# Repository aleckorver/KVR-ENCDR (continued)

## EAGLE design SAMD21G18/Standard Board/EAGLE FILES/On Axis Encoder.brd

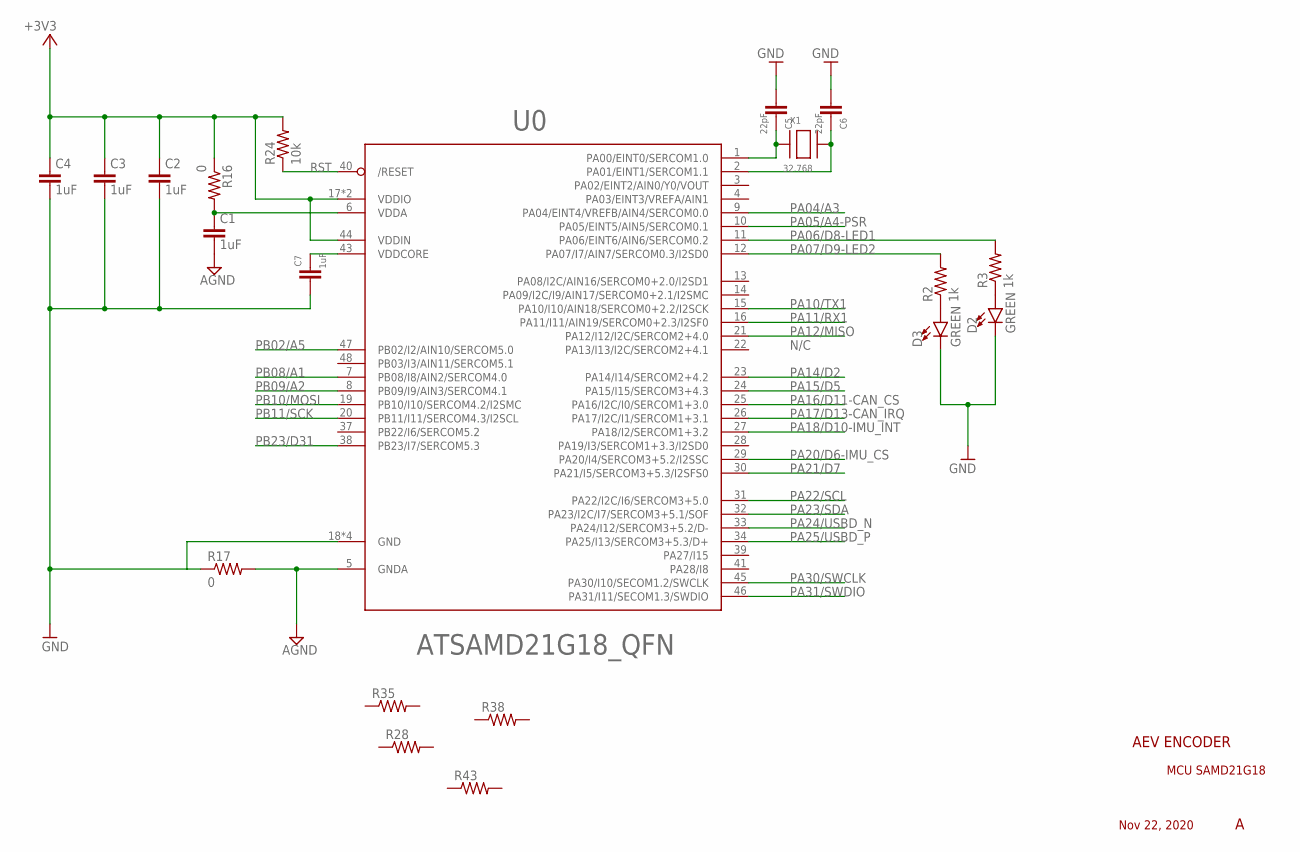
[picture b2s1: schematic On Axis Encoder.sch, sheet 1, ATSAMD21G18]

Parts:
C1, C2, C3, C4, C7: 1uF; C0805
C5, C6: 22pF; C0805
D2, D3: GREEN; LED-0603
R2, R3: 1k; R0603
R16, R17: 0; R0805
R24: 10k; R0805
R28: R-US_R0603; R0603
R35: R-US_R0402; R0402
R38: R-US_R0201; R0201
R43: R-US_R0805; R0805
U0: ATSAMD21G18_QFN; MICROBUILDER_TQFN48_7MM
X1: 32.768; XTAL3215

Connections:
+3V3: C2.1, C3.1, C4.1, R16.1, R24.2, U0.17 (VDDIO), U0.36 (VDDIO), U0.44 (VDDIN); also elsewhere on the board
AGND: C1.2, R17.2, U0.5 (GNDA); also elsewhere on the board
GND: C2.2, C3.2, C4.2, C5.2, C6.2, C7.2, D2.C, D3.C, R17.1, U0.18 (GND), U0.35 (GND), U0.42 (GND), U0.THERMAL (GND); also elsewhere on the board
unnamed: D2.A, R3.1
unnamed: D3.A, R2.1
unnamed: C5.1, U0.1 (PA00/EINT0/SERCOM1.0), X1.P$1
unnamed: C6.1, U0.2 (PA01/EINT1/SERCOM1.1), X1.P$2
unnamed: C1.1, R16.2, U0.6 (VDDA)
PA04/A3: U0.9 (PA04/EINT4/VREFB/AIN4/SERCOM0.0)
PA05/A4-PSR: U0.10 (PA05/EINT5/AIN5/SERCOM0.1); also elsewhere on the board
PA06/D8-LED1: R3.2, U0.11 (PA06/EINT6/AIN6/SERCOM0.2)
PA07/D9-LED2: R2.2, U0.12 (PA07/I7/AIN7/SERCOM0.3/I2SD0)
PA10/TX1: U0.15 (PA10/I10/AIN18/SERCOM0+2.2/I2SCK)
PA11/RX1: U0.16 (PA11/I11/AIN19/SERCOM0+2.3/I2SF0)
PA12/MISO: U0.21 (PA12/I12/I2C/SERCOM2+4.0); also elsewhere on the board
PA14/D2: U0.23 (PA14/I14/SERCOM2+4.2)
PA15/D5: U0.24 (PA15/I15/SERCOM3+4.3)
PA16/D11-CAN_CS: U0.25 (PA16/I2C/I0/SERCOM1+3.0); also elsewhere on the board
PA17/D13-CAN_IRQ: U0.26 (PA17/I2C/I1/SERCOM1+3.1); also elsewhere on the board
PA18/D10-IMU_INT: U0.27 (PA18/I2/SERCOM1+3.2); also elsewhere on the board
PA20/D6-IMU_CS: U0.29 (PA20/I4/SERCOM3+5.2/I2SSC); also elsewhere on the board
PA21/D7: U0.30 (PA21/I5/SERCOM3+5.3/I2SFS0)
PA22/SCL: U0.31 (PA22/I2C/I6/SERCOM3+5.0); also elsewhere on the board
PA23/SDA: U0.32 (PA23/I2C/I7/SERCOM3+5.1/SOF); also elsewhere on the board
PA24/USBD_N: U0.33 (PA24/I12/SERCOM3+5.2/D-); also elsewhere on the board
PA25/USBD_P: U0.34 (PA25/I13/SERCOM3+5.3/D+); also elsewhere on the board
PA30/SWCLK: U0.45 (PA30/I10/SECOM1.2/SWCLK); also elsewhere on the board
PA31/SWDIO: U0.46 (PA31/I11/SECOM1.3/SWDIO); also elsewhere on the board
PB02/A5: U0.47 (PB02/I2/AIN10/SERCOM5.0)
PB08/A1: U0.7 (PB08/I8/AIN2/SERCOM4.0)
PB09/A2: U0.8 (PB09/I9/AIN3/SERCOM4.1)
PB10/MOSI: U0.19 (PB10/I10/SERCOM4.2/I2SMC); also elsewhere on the board
PB11/SCK: U0.20 (PB11/I11/SERCOM4.3/I2SCL); also elsewhere on the board
PB23/D31: U0.38 (PB23/I7/SERCOM5.3)
RST: R24.1, U0.40 (/RESET); also elsewhere on the board
VDDCORE2: C7.1, U0.43 (VDDCORE)

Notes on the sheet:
N/C
AEV ENCODER
MCU SAMD21G18
Nov 22, 2020

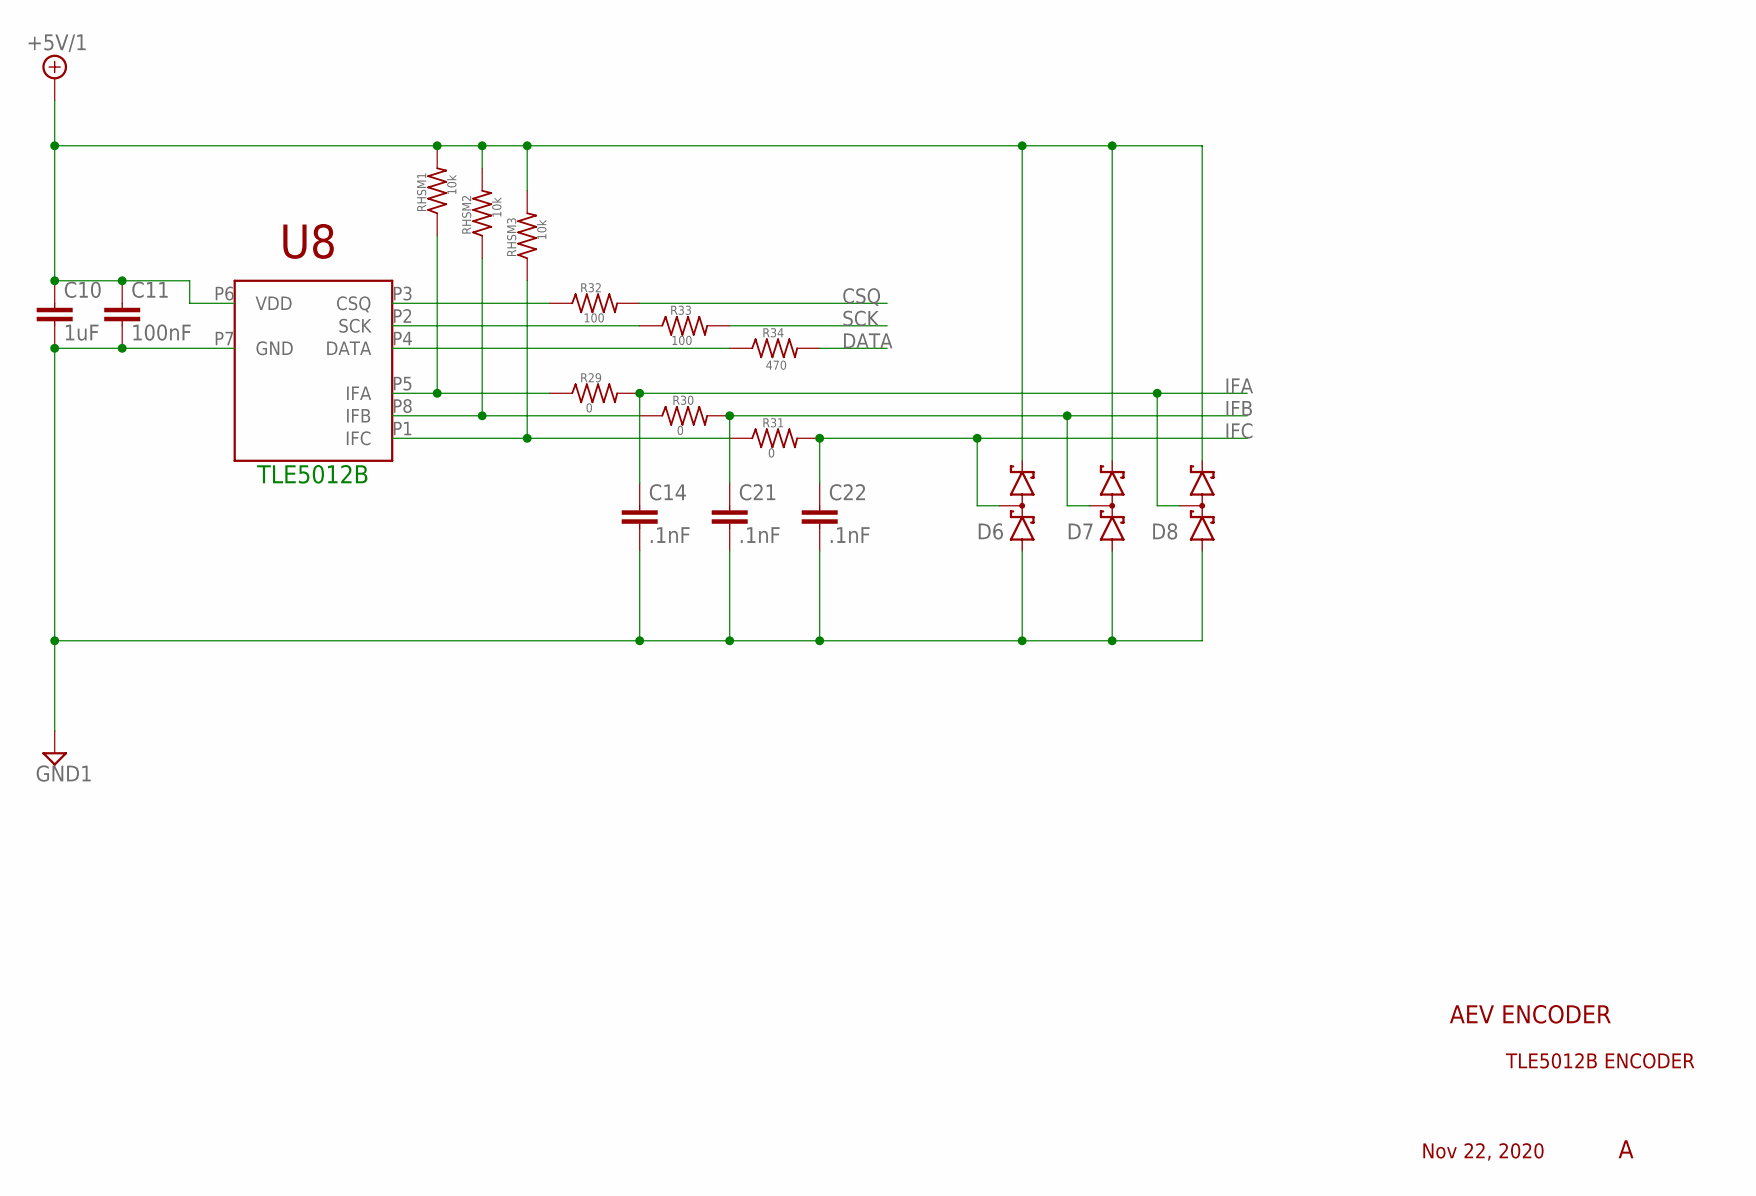
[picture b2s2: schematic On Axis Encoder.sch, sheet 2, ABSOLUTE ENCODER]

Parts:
C10: 1uF; C0805
C11: 100nF; C0805
C14, C21, C22: .1nF; C0805
D6, D7, D8: BAS70-04; SOT23
R29, R30, R31: 0; R0805
R32, R33: 100; R0805
R34: 470; R0805
RHSM1, RHSM2, RHSM3: 10k; R0805
U8: TLE5012B; PG-DSO-8

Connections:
+5V/1: C10.1, C11.1, D6.2 (C2), D7.2 (C2), D8.2 (C2), RHSM1.2, RHSM2.2, RHSM3.2, U8.P6 (VDD); also elsewhere on the board
CSQ: R32.2; also elsewhere on the board
DATA: R34.2; also elsewhere on the board
GND1: C10.2, C11.2, C14.2, C21.2, C22.2, D6.1 (A1), D7.1 (A1), D8.1 (A1), U8.P7 (GND); also elsewhere on the board
IFA: C14.1, D8.3 (C1A2), R29.2; also elsewhere on the board
IFB: C21.1, D7.3 (C1A2), R30.2; also elsewhere on the board
IFC: C22.1, D6.3 (C1A2), R31.2; also elsewhere on the board
unnamed: R32.1, U8.P3 (CSQ)
unnamed: R33.1, U8.P2 (SCK)
unnamed: R34.1, U8.P4 (DATA)
unnamed: R29.1, RHSM1.1, U8.P5 (IFA)
unnamed: R30.1, RHSM2.1, U8.P8 (IFB)
unnamed: R31.1, RHSM3.1, U8.P1 (IFC)
SCK: R33.2; also elsewhere on the board

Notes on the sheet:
TLE5012B
AEV ENCODER
TLE5012B ENCODER
Nov 22, 2020

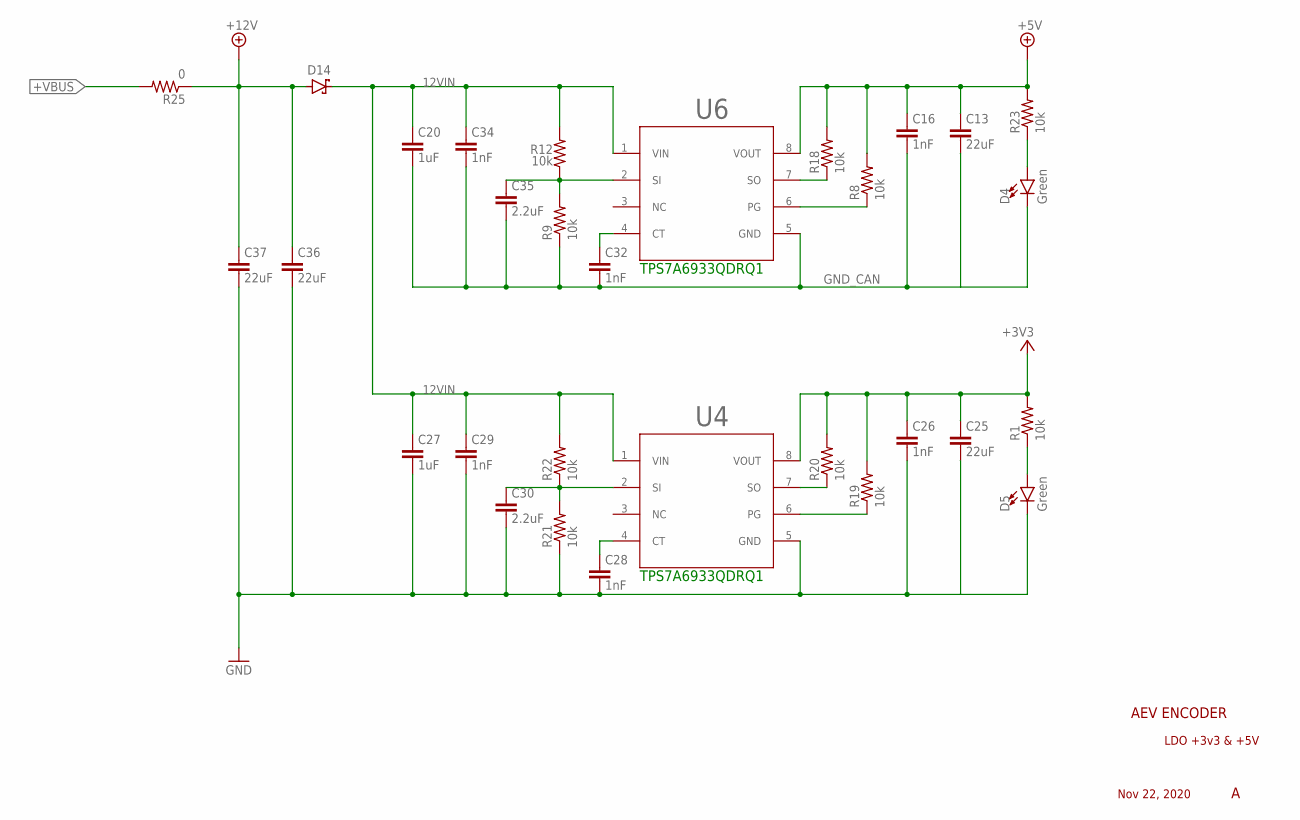
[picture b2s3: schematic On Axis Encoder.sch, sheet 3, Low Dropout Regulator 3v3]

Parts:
C13, C25: 22uF; C0805
C16, C26, C28, C29, C32, C34: 1nF; C0805
C20, C27: 1uF; C0805
C30, C35: 2.2uF; C0805
C36, C37: 22uF; C1206
D4, D5: Green; LED-1206-BOTTOM
D14: MBR0520LT1G; SODFL3718X115
R1, R8, R9, R12, R18, R19, R20, R21, R22, R23: 10k; R0805
R25: 0; R0805
U4, U6: Value; D0008A_N

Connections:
12VIN: C20.1, C27.1, C29.1, C34.1, D14.1 (C), R12.2, R22.2, U4.1 (VIN), U6.1 (VIN)
+3V3: C25.1, C26.1, R1.2, R19.2, R20.2, U4.8 (VOUT); also elsewhere on the board
+5V: C13.1, C16.1, R8.2, R18.2, R23.2, U6.8 (VOUT); also elsewhere on the board
+12V: C36.1, C37.1, D14.2 (A), R25.1; also elsewhere on the board
+VBUS: R25.2; also elsewhere on the board
GND: C25.2, C26.2, C27.2, C28.2, C29.2, C30.2, C36.2, C37.2, D5.C, R21.1, U4.5 (GND); also elsewhere on the board
GND_CAN: C13.2, C16.2, C20.2, C32.2, C34.2, C35.2, D4.C, R9.1, U6.5 (GND); also elsewhere on the board
unnamed: D5.A, R1.1
unnamed: C35.1, R9.2, R12.1, U6.2 (SI)
unnamed: C30.1, R21.2, R22.1, U4.2 (SI)
unnamed: R19.1, U4.6 (PG)
unnamed: R20.1, U4.7 (SO)
unnamed: C28.1, U4.4 (CT)
unnamed: R8.1, U6.6 (PG)
unnamed: R18.1, U6.7 (SO)
unnamed: C32.1, U6.4 (CT)
unnamed: D4.A, R23.1

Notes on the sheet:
TPS7A6933QDRQ1
AEV ENCODER
LDO +3v3 & +5V
Nov 22, 2020

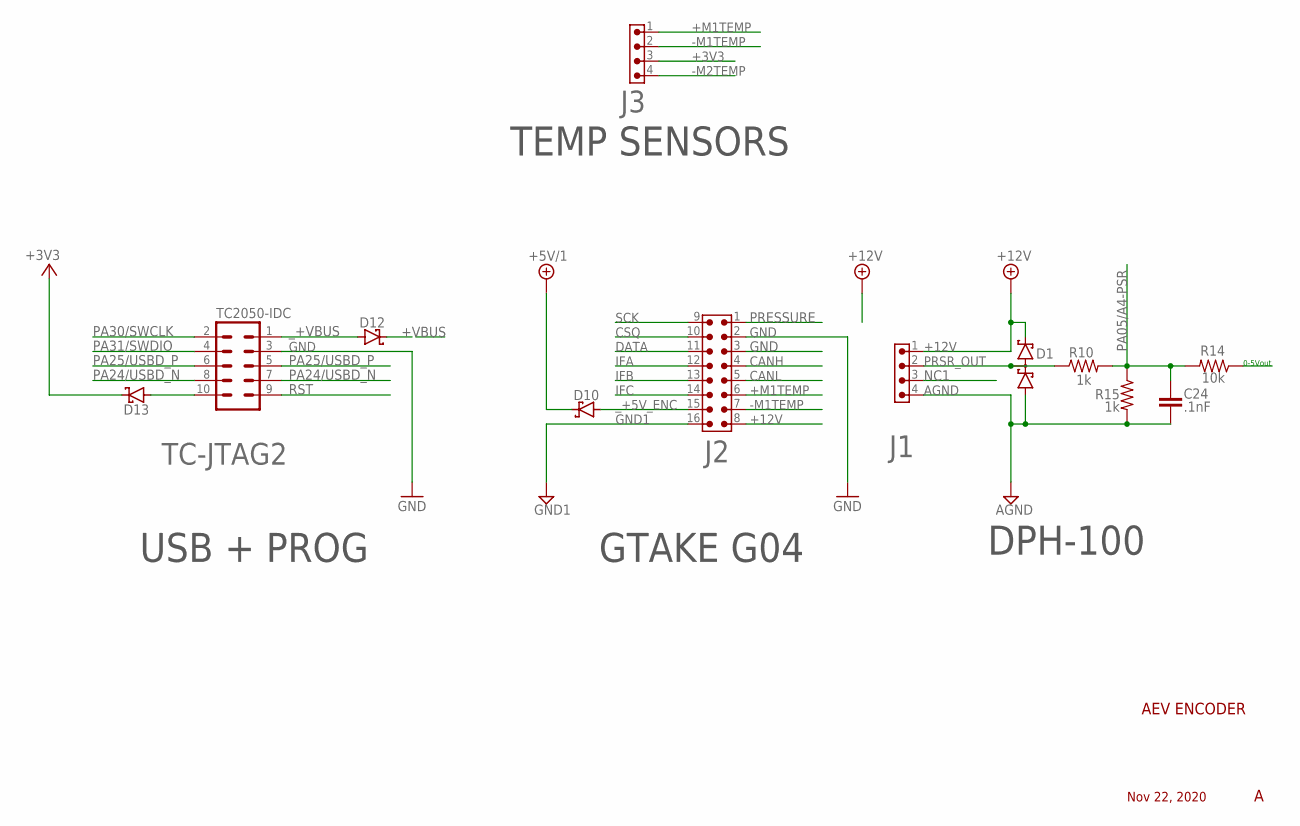
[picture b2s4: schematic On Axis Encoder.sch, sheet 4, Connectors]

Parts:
C24: .1nF; C0805
D1: BAS70-04; SOT23
D10, D12, D13: MBR0520LT1G; SODFL3718X115
J1, J3: 6620XX11122_66200411122; 66200411122
J2: 6620XX21122_66201621122; 66201621122
R10, R15: 1k; R0805
R14: 10k; R0805
TC-JTAG2: TC2050-IDC

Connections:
+3V3: D13.1 (C), J3.3; also elsewhere on the board
+5V/1: D10.1 (C); also elsewhere on the board
+12V: D1.2 (C2), J1.1, J2.8; also elsewhere on the board
+M1TEMP: J2.6, J3.1
+VBUS: D12.1 (C); also elsewhere on the board
-M1TEMP: J2.7, J3.2
-M2TEMP: J3.4; also elsewhere on the board
AGND: C24.2, D1.1 (A1), J1.4, R15.2; also elsewhere on the board
CANH: J2.4; also elsewhere on the board
CANL: J2.5; also elsewhere on the board
CSQ: J2.10; also elsewhere on the board
DATA: J2.11; also elsewhere on the board
GND: J2.2, J2.3, TC-JTAG2.3; also elsewhere on the board
GND1: J2.16; also elsewhere on the board
IFA: J2.12; also elsewhere on the board
IFB: J2.13; also elsewhere on the board
IFC: J2.14; also elsewhere on the board
unnamed: D13.2 (A), TC-JTAG2.10
NC1: J1.3
PA05/A4-PSR: C24.1, R10.2, R14.2, R15.1; also elsewhere on the board
PA24/USBD_N: TC-JTAG2.7, TC-JTAG2.8; also elsewhere on the board
PA25/USBD_P: TC-JTAG2.5, TC-JTAG2.6; also elsewhere on the board
PA30/SWCLK: TC-JTAG2.2; also elsewhere on the board
PA31/SWDIO: TC-JTAG2.4; also elsewhere on the board
PRESSURE: J2.1, R14.1
PRSR_OUT: D1.3 (C1A2), J1.2, R10.1
RST: TC-JTAG2.9; also elsewhere on the board
SCK: J2.9; also elsewhere on the board
_+5V_ENC: D10.2 (A), J2.15
_+VBUS: D12.2 (A), TC-JTAG2.1

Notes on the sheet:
USB + PROG
0-5Vout
AEV ENCODER
Nov 22, 2020
GTAKE G04
DPH-100
TEMP SENSORS

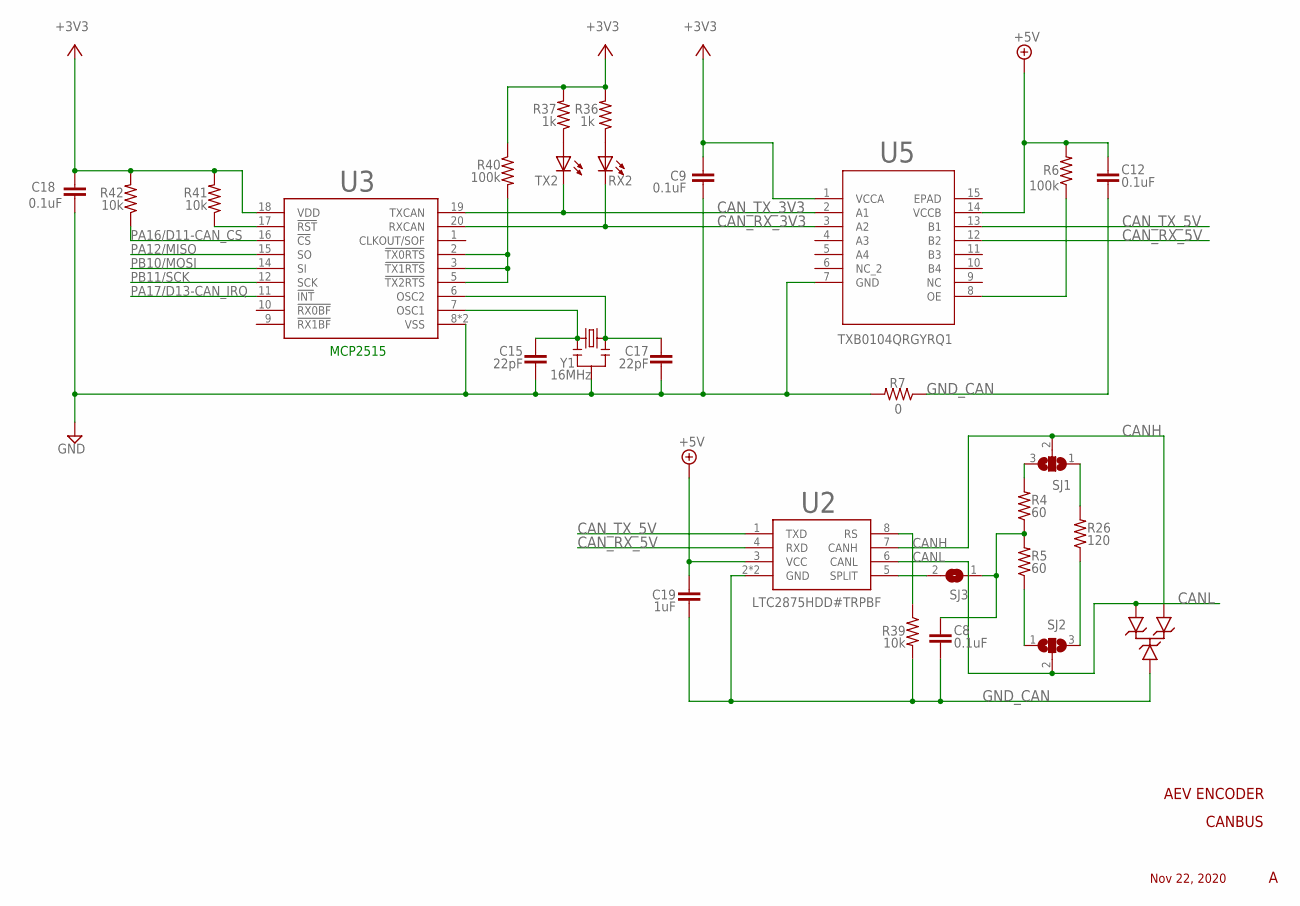
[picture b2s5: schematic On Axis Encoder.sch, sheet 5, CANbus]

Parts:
C8, C9, C12, C18: 0.1uF; C0805
C15, C17: 22pF; C0805
C19: 1uF; C0805
R4, R5: 60; R0805
R6, R40: 100k; R0805
R7: 0; R0805
R26: 120; R0805
R36, R37: 1k; R0805
R39, R41, R42: 10k; R0805
RX2: LEDCHIPLED_0805; CHIPLED_0805
SJ1, SJ2: SJ2W; SJ_2
SJ3: SJ
TX2: LEDCHIPLED_0805; CHIPLED_0805
U2: LTC2875HDD#TRPBF; SON50P300X300X80-9T165X238N
U3: MCP2515-E/ML; QFN50P400X400X100-21T270N
U5: TXB0104QRGYRQ1; RGY14_2P05X2P05
U$2: μCLAMP2492SQ; SOT-23_3L_ONS
Y1: 16MHz; RESONATOR-SMD

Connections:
+3V3: C9.1, C18.1, R36.2, R37.2, R40.1, R41.2, R42.2, U3.18 (VDD), U5.1 (VCCA); also elsewhere on the board
+5V: C12.1, C19.1, R6.2, U2.3 (VCC), U5.14 (VCCB); also elsewhere on the board
CANH: SJ1.2, U2.7 (CANH), U$2.2; also elsewhere on the board
CANL: SJ2.2, U2.6 (CANL), U$2.1; also elsewhere on the board
CAN_RX_3V3: RX2.C, U3.20 (RXCAN), U5.3 (A2)
CAN_RX_5V: U2.4 (RXD), U5.12 (B2)
CAN_TX_3V3: TX2.C, U3.19 (TXCAN), U5.2 (A1)
CAN_TX_5V: U2.1 (TXD), U5.13 (B1)
GND: C9.2, C15.2, C17.2, C18.2, R7.2, U3.8 (VSS), U3.21 (VSS), U5.7 (GND), Y1.2; also elsewhere on the board
GND_CAN: C8.2, C12.2, C19.2, R7.1, R39.2, U2.2 (GND), U2.9 (GND), U$2.3; also elsewhere on the board
unnamed: R6.1, U5.8 (OE)
unnamed: R39.1, U2.8 (RS)
unnamed: SJ3.2, U2.5 (SPLIT)
unnamed: R36.1, RX2.A
unnamed: R37.1, TX2.A
unnamed: R41.1, U3.17 (!RST)
unnamed: R40.2, U3.2 (!TX0RTS), U3.3 (!TX1RTS), U3.5 (!TX2RTS)
unnamed: C17.1, U3.6 (OSC2), Y1.3
unnamed: C15.1, U3.7 (OSC1), Y1.1
PA12/MISO: U3.15 (SO); also elsewhere on the board
PA16/D11-CAN_CS: R42.1, U3.16 (!CS); also elsewhere on the board
PA17/D13-CAN_IRQ: U3.11 (!INT); also elsewhere on the board
PB10/MOSI: U3.14 (SI); also elsewhere on the board
PB11/SCK: U3.12 (SCK); also elsewhere on the board
RSH: R4.2, SJ1.3
RSL: R5.1, SJ2.1
RTH: R26.2, SJ1.1
RTL: R26.1, SJ2.3
SPLIT: C8.1, R4.1, R5.2, SJ3.1

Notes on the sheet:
MCP2515
CANBUS
AEV ENCODER
Nov 22, 2020

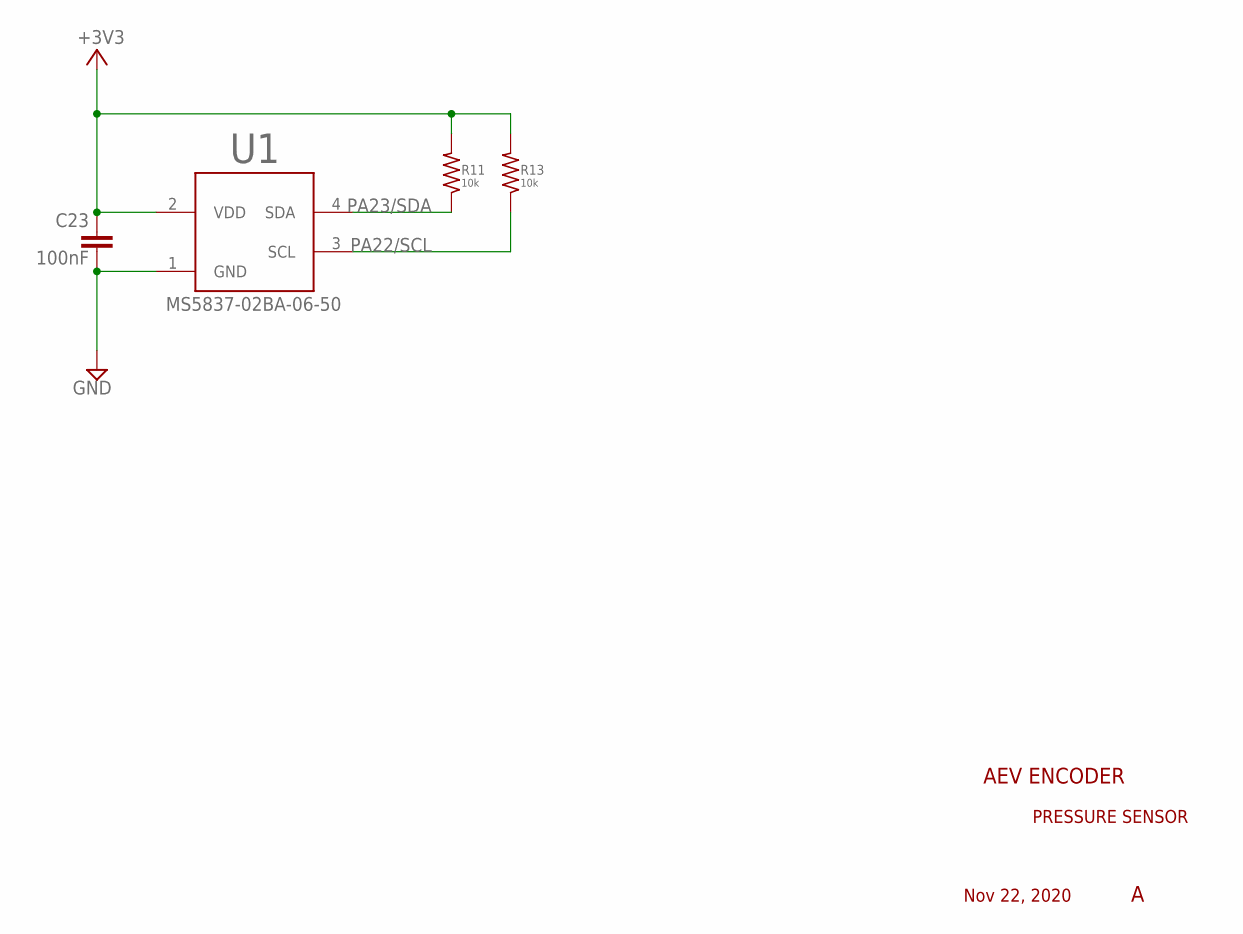
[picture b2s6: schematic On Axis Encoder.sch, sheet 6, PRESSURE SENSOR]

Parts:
C23: 100nF; C0603
R11, R13: 10k; R0603
U1: MS5837-02BA-06-50; DFN330X330X275-4N

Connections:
+3V3: C23.1, R11.2, R13.2, U1.2 (VDD); also elsewhere on the board
GND: C23.2, U1.1 (GND); also elsewhere on the board
PA22/SCL: R13.1, U1.3 (SCL); also elsewhere on the board
PA23/SDA: R11.1, U1.4 (SDA); also elsewhere on the board

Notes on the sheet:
AEV ENCODER
PRESSURE SENSOR
Nov 22, 2020

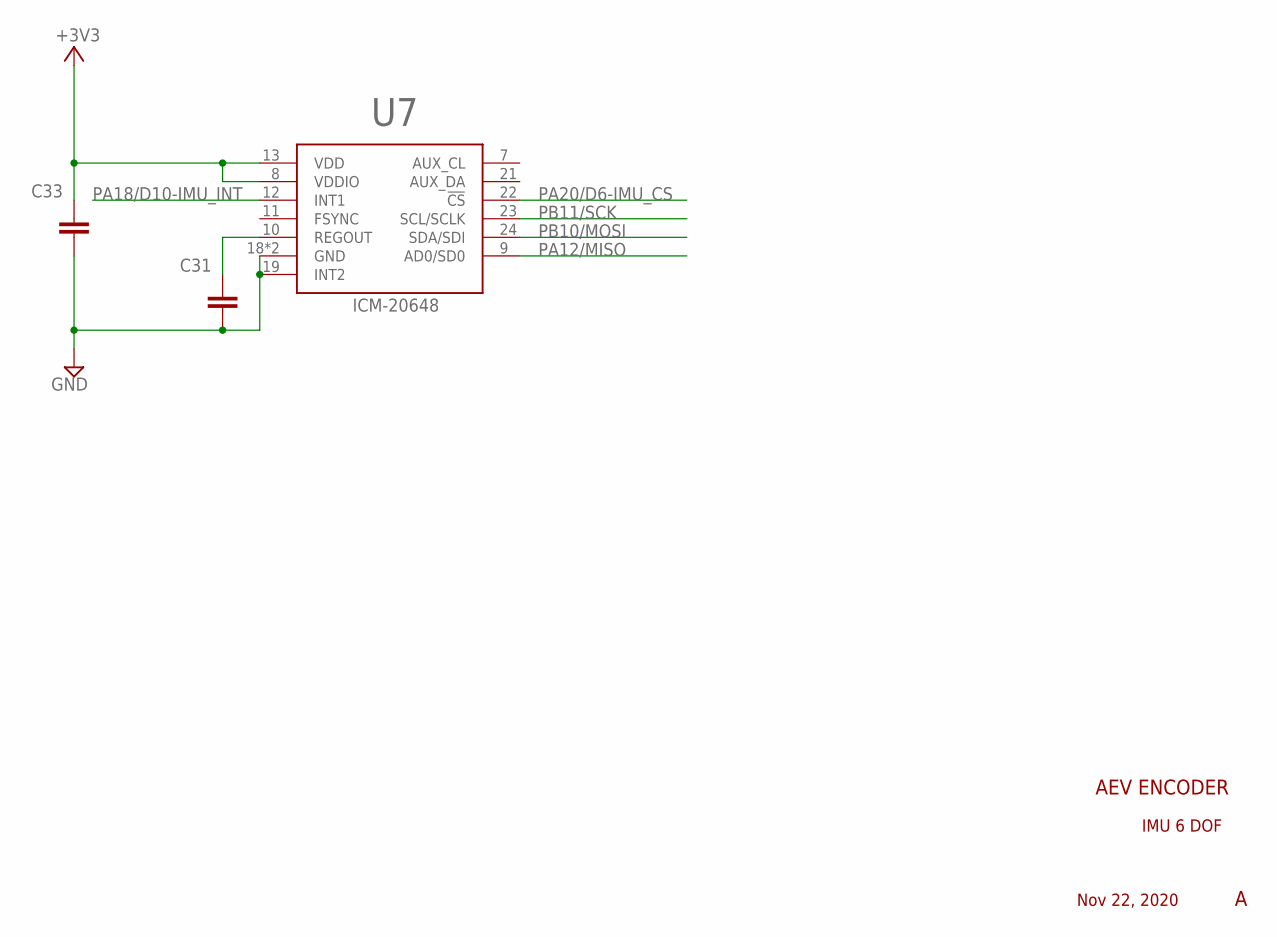
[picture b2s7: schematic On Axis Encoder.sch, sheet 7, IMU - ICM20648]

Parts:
C31, C33: 0.1uF; 0603
U7: ICM-20648

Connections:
+3V3: C33.P$1 (1), U7.8 (VDDIO), U7.13 (VDD); also elsewhere on the board
GND: C31.P$2 (2), C33.P$2 (2), U7.18 (GND), U7.19 (INT2), U7.20 (GND); also elsewhere on the board
PA12/MISO: U7.9 (AD0/SD0); also elsewhere on the board
PA18/D10-IMU_INT: U7.12 (INT1); also elsewhere on the board
PA20/D6-IMU_CS: U7.22 (!CS); also elsewhere on the board
PB10/MOSI: U7.24 (SDA/SDI); also elsewhere on the board
PB11/SCK: U7.23 (SCL/SCLK); also elsewhere on the board
REGOUT2: C31.P$1 (1), U7.10 (REGOUT)

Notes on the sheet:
AEV ENCODER
IMU 6 DOF
Nov 22, 2020

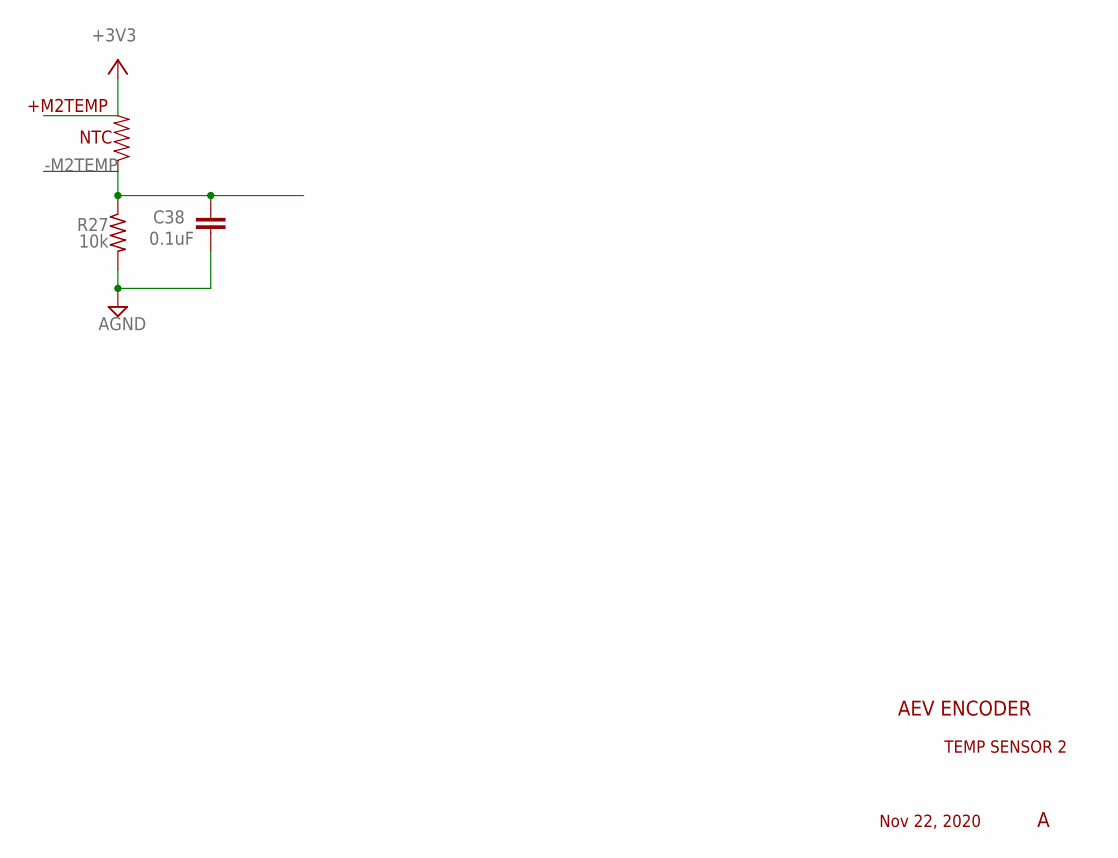
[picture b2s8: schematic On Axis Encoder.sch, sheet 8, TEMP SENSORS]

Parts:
C38: 0.1uF; C0805
R27: 10k; R0805

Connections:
-M2TEMP: C38.1, R27.1; also elsewhere on the board
AGND: C38.2, R27.2; also elsewhere on the board

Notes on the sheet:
NTC
+M2TEMP
AEV ENCODER
TEMP SENSOR 2
Nov 22, 2020

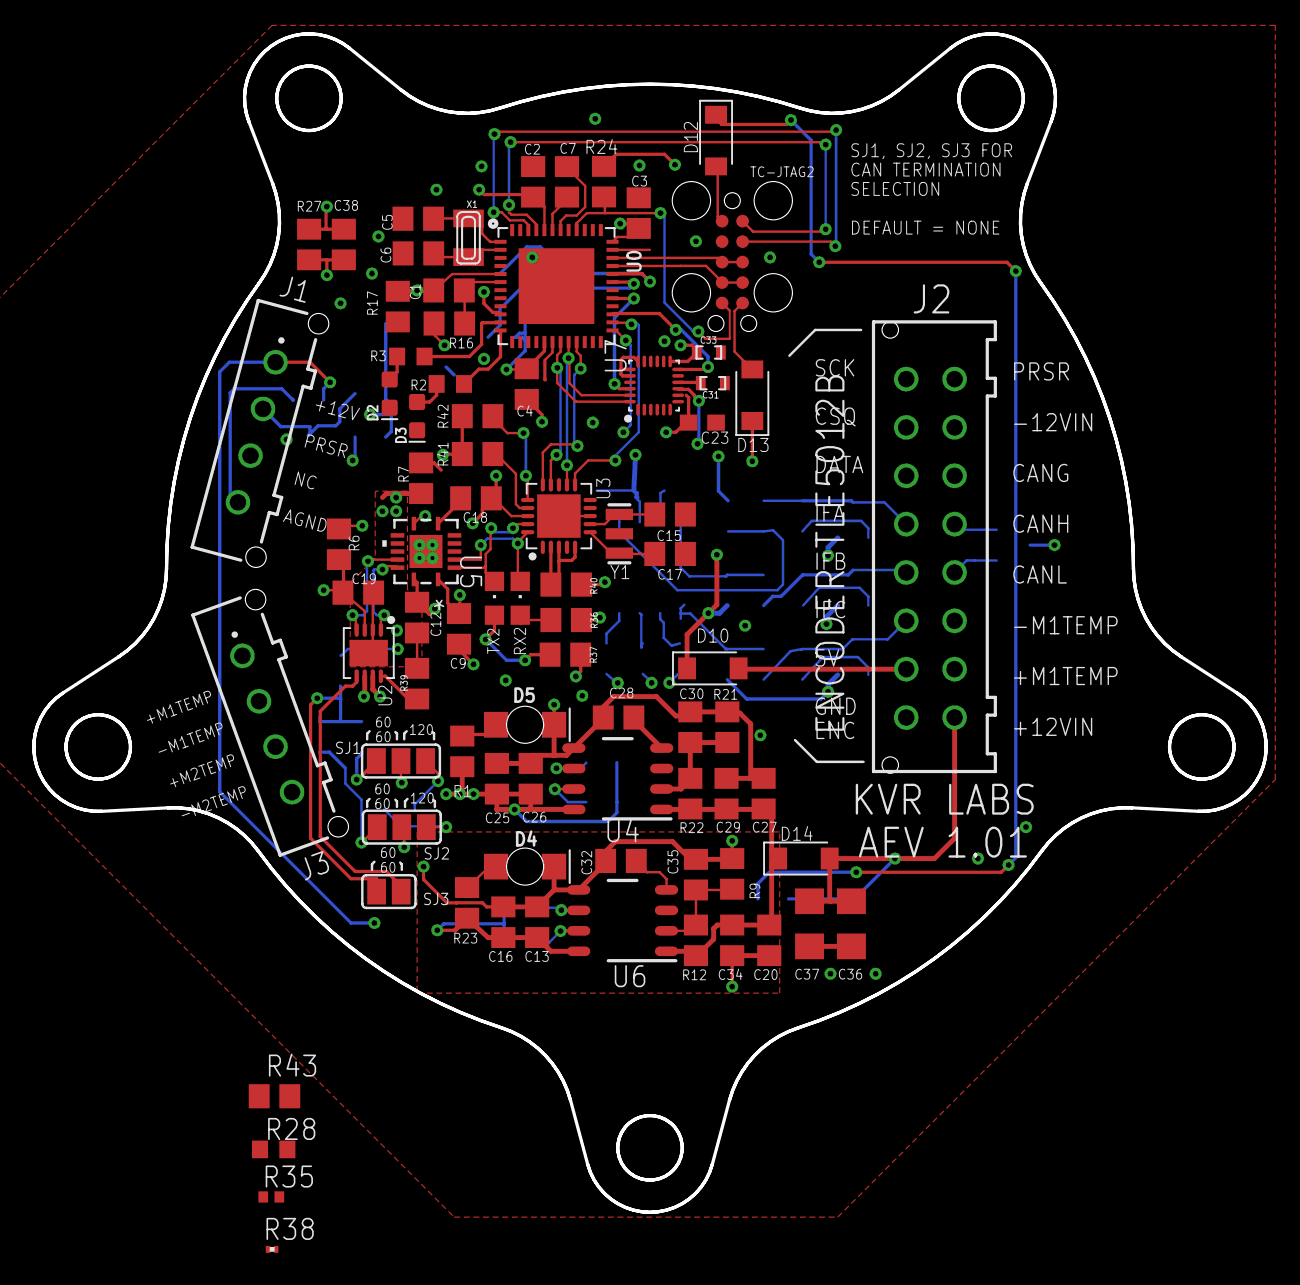
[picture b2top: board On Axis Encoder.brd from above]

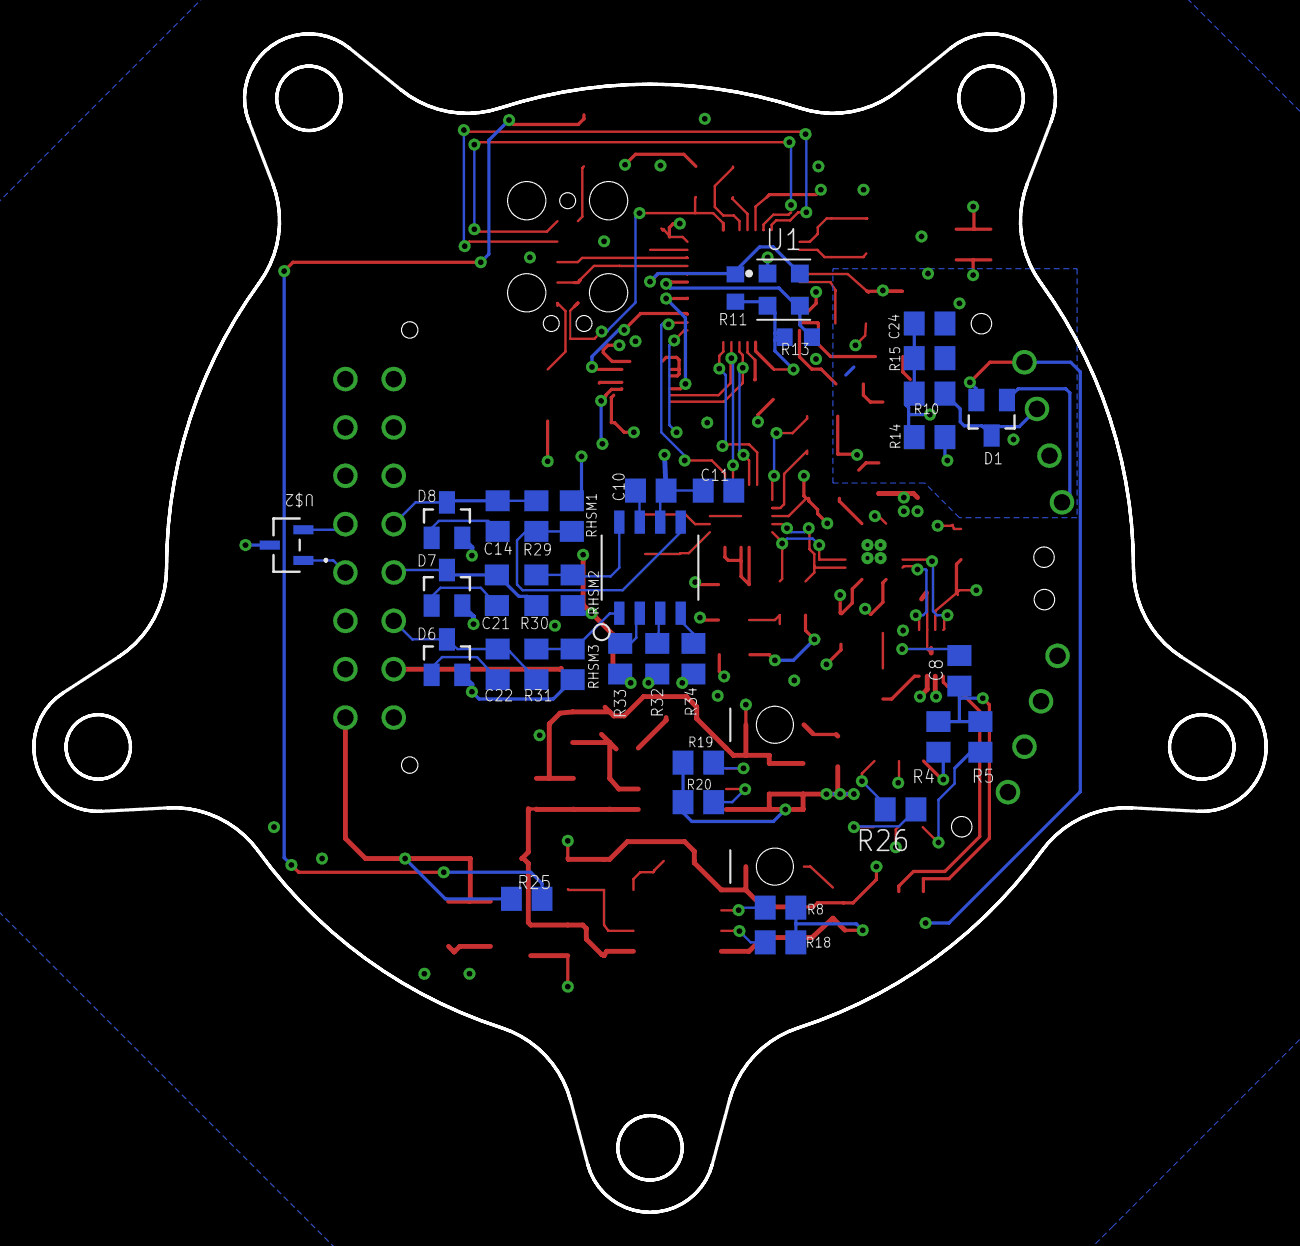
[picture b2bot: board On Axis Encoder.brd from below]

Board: 4 copper layers, 76.5 x 73.1 mm, 117 parts (36 on the bottom side), 84 nets.

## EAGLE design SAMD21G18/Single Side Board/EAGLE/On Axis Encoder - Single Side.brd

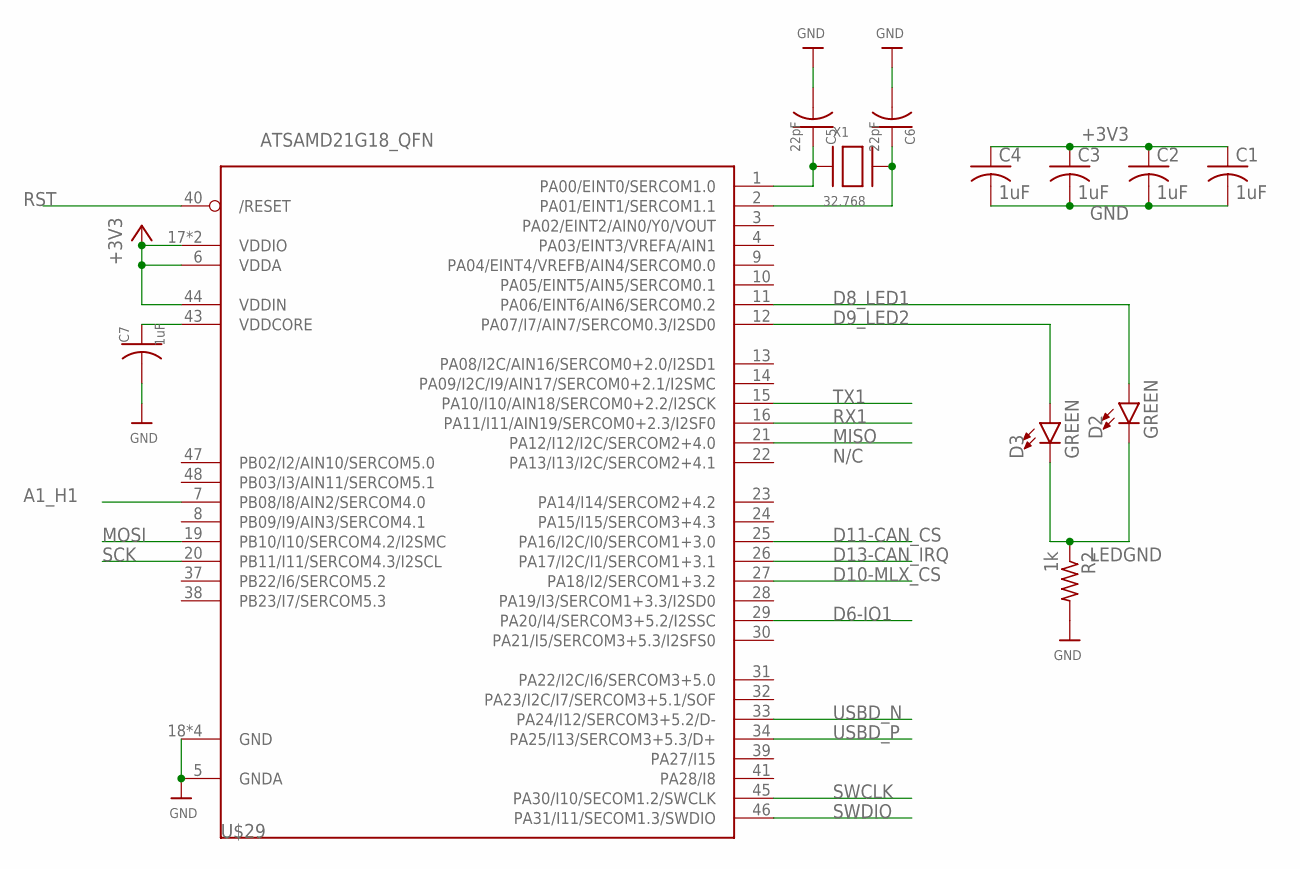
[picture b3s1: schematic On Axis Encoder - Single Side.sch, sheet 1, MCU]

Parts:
C1, C2, C3, C4, C7: 1uF; C0603
C5, C6: 22pF; C0603
D2, D3: GREEN; LED-0603
R2: 1k; R0603
U$29: ATSAMD21G18_QFN; MICROBUILDER_TQFN48_7MM
X1: 32.768; XTAL3215

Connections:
+3V3: C1.1, C2.1, C3.1, C4.1, U$29.6 (VDDA), U$29.17 (VDDIO), U$29.36 (VDDIO), U$29.44 (VDDIN); also elsewhere on the board
A1_H1: U$29.7 (PB08/I8/AIN2/SERCOM4.0); also elsewhere on the board
D6-IO1: U$29.29 (PA20/I4/SERCOM3+5.2/I2SSC); also elsewhere on the board
D8_LED1: D2.A, U$29.11 (PA06/EINT6/AIN6/SERCOM0.2)
D9_LED2: D3.A, U$29.12 (PA07/I7/AIN7/SERCOM0.3/I2SD0)
D10-MLX_CS: U$29.27 (PA18/I2/SERCOM1+3.2); also elsewhere on the board
D11-CAN_CS: U$29.25 (PA16/I2C/I0/SERCOM1+3.0); also elsewhere on the board
D13-CAN_IRQ: U$29.26 (PA17/I2C/I1/SERCOM1+3.1); also elsewhere on the board
GND: C1.2, C2.2, C3.2, C4.2, C5.2, C6.2, C7.2, R2.2, U$29.5 (GNDA), U$29.18 (GND), U$29.35 (GND), U$29.42 (GND), U$29.THERMAL (GND); also elsewhere on the board
LEDGND: D2.C, D3.C, R2.1; also elsewhere on the board
MISO: U$29.21 (PA12/I12/I2C/SERCOM2+4.0); also elsewhere on the board
MOSI: U$29.19 (PB10/I10/SERCOM4.2/I2SMC); also elsewhere on the board
unnamed: C5.1, U$29.1 (PA00/EINT0/SERCOM1.0), X1.P$1
unnamed: C6.1, U$29.2 (PA01/EINT1/SERCOM1.1), X1.P$2
RST: U$29.40 (/RESET); also elsewhere on the board
RX1: U$29.16 (PA11/I11/AIN19/SERCOM0+2.3/I2SF0)
SCK: U$29.20 (PB11/I11/SERCOM4.3/I2SCL); also elsewhere on the board
SWCLK: U$29.45 (PA30/I10/SECOM1.2/SWCLK); also elsewhere on the board
SWDIO: U$29.46 (PA31/I11/SECOM1.3/SWDIO); also elsewhere on the board
TX1: U$29.15 (PA10/I10/AIN18/SERCOM0+2.2/I2SCK)
USBD_N: U$29.33 (PA24/I12/SERCOM3+5.2/D-); also elsewhere on the board
USBD_P: U$29.34 (PA25/I13/SERCOM3+5.3/D+); also elsewhere on the board
VDDCORE2: C7.1, U$29.43 (VDDCORE)

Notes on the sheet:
N/C

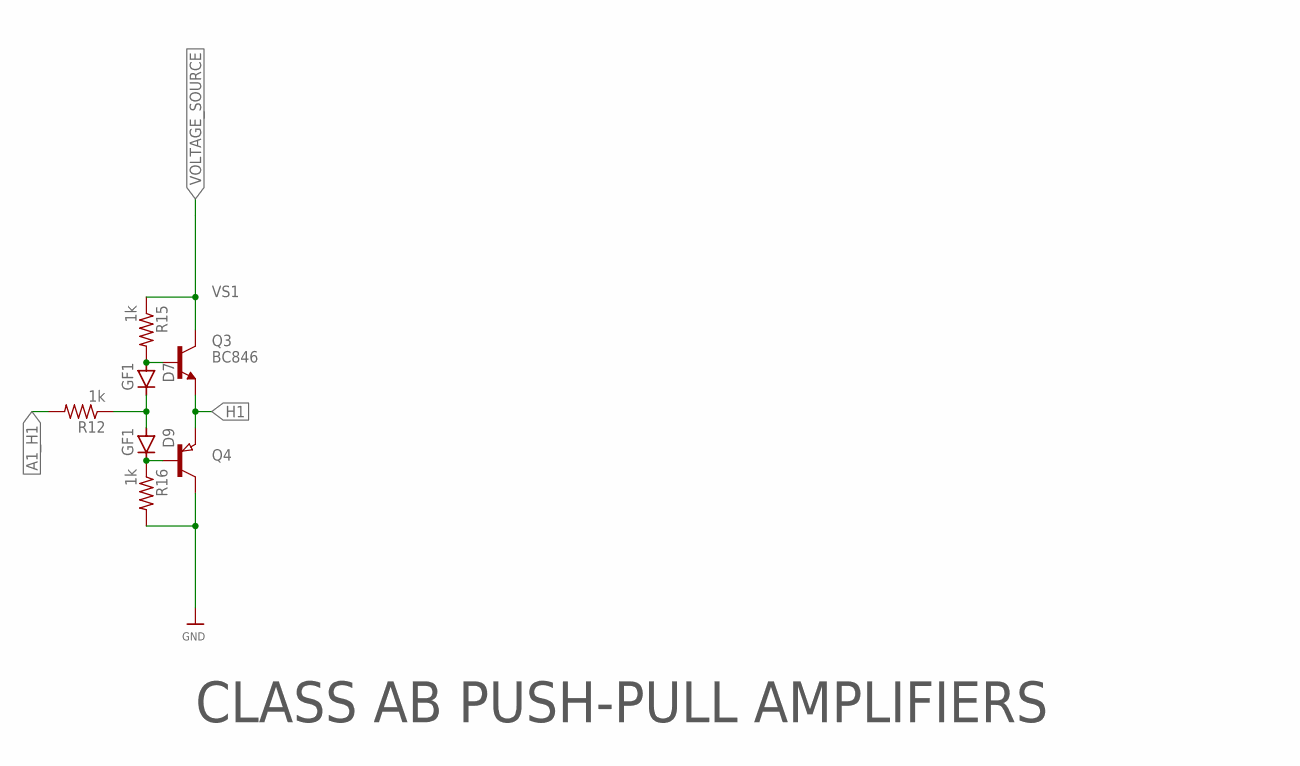
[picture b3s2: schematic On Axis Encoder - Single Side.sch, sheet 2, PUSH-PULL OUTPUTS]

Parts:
D7, D9: GF1; SMA-DO214AC
Q3: BC846; SOT23
Q4: PNP-TRANSISTOR_SOT23; SOT23
R12, R15, R16: 1k; R0603

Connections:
A1_H1: R12.2; also elsewhere on the board
GND: Q4.3 (C), R16.2; also elsewhere on the board
H1: Q3.2 (E), Q4.2 (E); also elsewhere on the board
unnamed: D9.K (C), Q4.1 (B), R16.1
unnamed: D7.A, Q3.1 (B), R15.2
unnamed: D7.K (C), D9.A, R12.1
VS1: Q3.3 (C), R15.1

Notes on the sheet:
CLASS AB PUSH-PULL AMPLIFIERS
